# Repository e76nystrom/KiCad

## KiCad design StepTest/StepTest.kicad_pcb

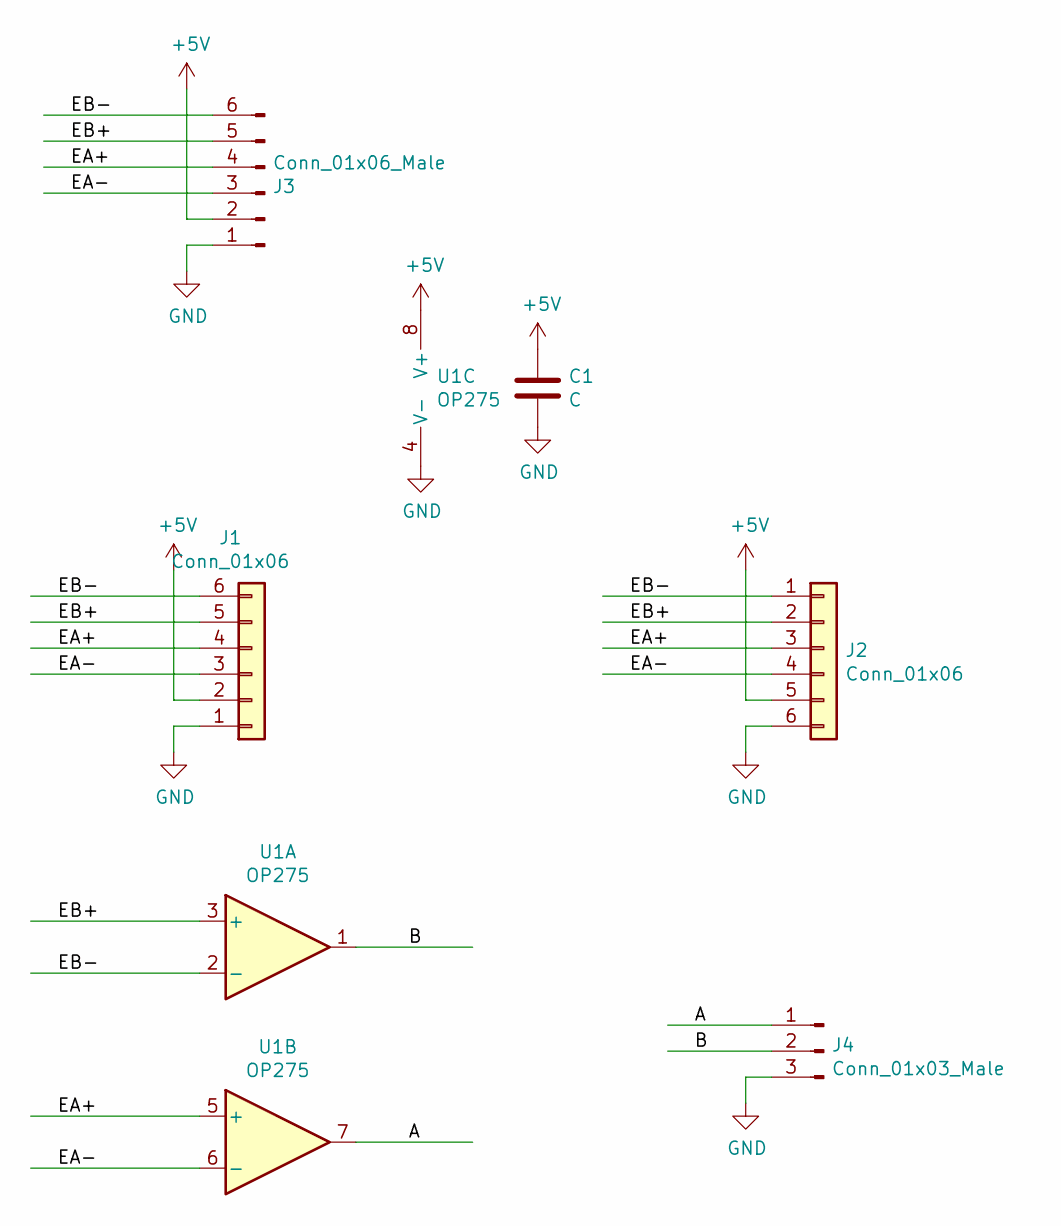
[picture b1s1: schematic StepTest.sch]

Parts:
C1: C; C_0805_2012Metric_Pad1.15x1.40mm_HandSolder
J1, J2: Conn_01x06; 6_Pin_3.81mm
J3: Conn_01x06_Male; PinHeader_1x06_P2.54mm_Vertical
J4: Conn_01x03_Male; PinHeader_1x03_P2.54mm_Vertical
U1: OP275; SOIC-8_3.9x4.9mm_P1.27mm

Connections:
+5V: C1.1, J1.2, J2.5, J3.2, U1.8 (V+)
/A: J4.1, U1.7
/B: J4.2, U1.1
/EA+: J1.4, J2.3, J3.4, U1.5 (+)
/EA-: J1.3, J2.4, J3.3, U1.6 (-)
/EB+: J1.5, J2.2, J3.5, U1.3 (+)
/EB-: J1.6, J2.1, J3.6, U1.2 (-)
GND: C1.2, J1.1, J2.6, J3.1, J4.3, U1.4 (V-)

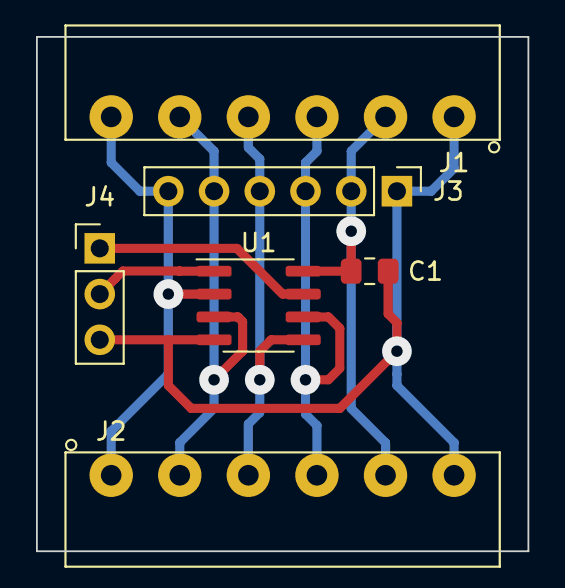
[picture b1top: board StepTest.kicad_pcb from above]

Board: 2 copper layers, 27.3 x 28.6 mm, 6 parts (0 on the bottom side), 8 nets.
